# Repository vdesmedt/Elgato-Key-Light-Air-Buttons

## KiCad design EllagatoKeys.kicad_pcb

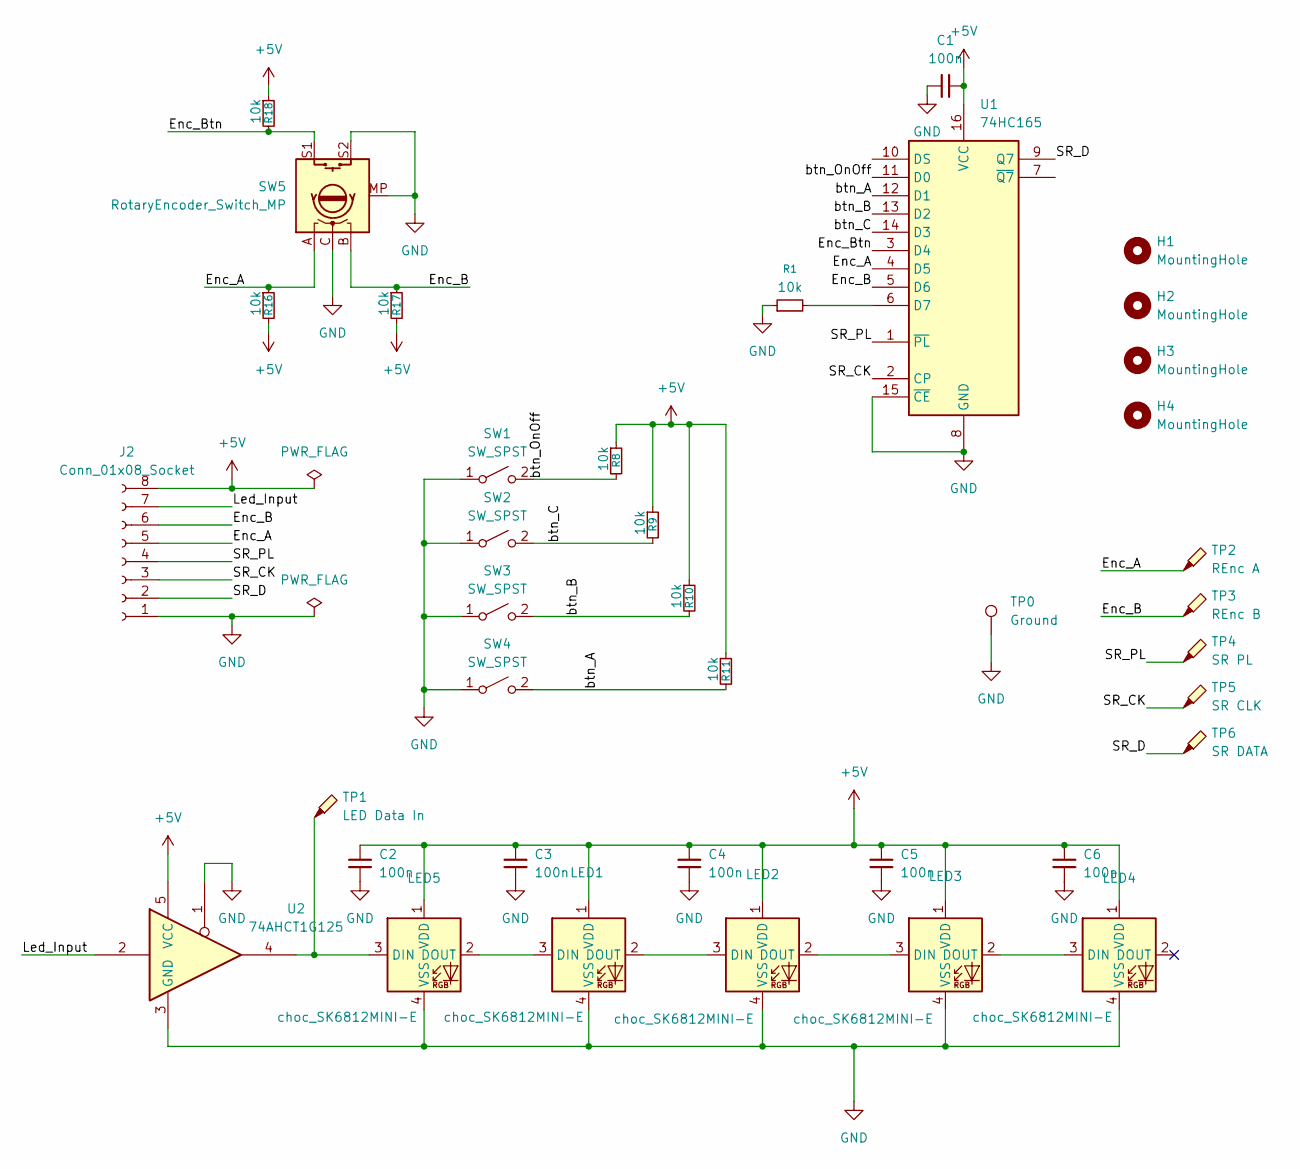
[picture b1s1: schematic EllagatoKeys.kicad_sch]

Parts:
C1, C2, C3, C4, C5, C6: 100n; C_0805_2012Metric_Pad1.18x1.45mm_HandSolder
H1, H2, H3, H4: MountingHole; MountingHole_2.7mm_M2.5
J2: Conn_01x08_Socket; PinHeader_1x08_P2.54mm_Horizontal
LED1, LED2, LED3, LED4, LED5: choc_SK6812MINI-E; LED_choc_6028R
R1, R8, R9, R10, R11, R16, R17, R18: 10k; R_0805_2012Metric_Pad1.20x1.40mm_HandSolder
SW1, SW2, SW3, SW4: SW_SPST; SW_Cherry_MX_1.00u_Plate
SW5: RotaryEncoder_Switch_MP; RotaryEncoder_Alps_EC11E-Switch_Vertical_H20mm
TP0: Ground; TestPoint_Keystone_5010-5014_Multipurpose
TP1: LED Data In; TestPoint_Keystone_5010-5014_Multipurpose
TP2: REnc A; TestPoint_Keystone_5010-5014_Multipurpose
TP3: REnc B; TestPoint_Keystone_5010-5014_Multipurpose
TP4: SR PL; TestPoint_Keystone_5010-5014_Multipurpose
TP5: SR CLK; TestPoint_Keystone_5010-5014_Multipurpose
TP6: SR DATA; TestPoint_Keystone_5010-5014_Multipurpose
U1: 74HC165; SOIC-16_3.9x9.9mm_P1.27mm
U2: 74AHCT1G125; SOT-23-5

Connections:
+5V: C1.2, C2.1, C3.1, C4.1, C5.1, C6.1, J2.8, LED1.1 (VDD), LED2.1 (VDD), LED3.1 (VDD), LED4.1 (VDD), LED5.1 (VDD), R8.1, R9.1, R10.1, R11.1, R16.2, R17.2, R18.1, U1.16 (VCC), U2.5 (VCC)
/Enc_A: J2.5, R16.1, SW5.A, TP2.1 (1_1), U1.4 (D5)
/Enc_B: J2.6, R17.1, SW5.B, TP3.1 (1_1), U1.5 (D6)
/Enc_Btn: R18.2, SW5.S1, U1.3 (D4)
/Led_Input: J2.7, U2.2
/SR_CK: J2.3, TP5.1 (1_1), U1.2 (CP)
/SR_D: J2.2, TP6.1 (1_1), U1.9 (Q7)
/SR_PL: J2.4, TP4.1 (1_1), U1.1 (~PL)
/btn_A: R11.2, SW4.2 (B), U1.12 (D1)
/btn_B: R10.2, SW3.2 (B), U1.13 (D2)
/btn_C: R9.2, SW2.2 (B), U1.14 (D3)
/btn_OnOff: R8.2, SW1.2 (B), U1.11 (D0)
GND: C1.1, C2.2, C3.2, C4.2, C5.2, C6.2, J2.1, LED1.4 (VSS), LED2.4 (VSS), LED3.4 (VSS), LED4.4 (VSS), LED5.4 (VSS), R1.1, SW1.1 (A), SW2.1 (A), SW3.1 (A), SW4.1 (A), SW5.C, SW5.MP, SW5.S2, TP0.1 (1_1), U1.8 (GND), U1.15 (~CE), U2.1, U2.3 (GND)
unnamed: LED1.3 (DIN), LED5.2 (DOUT)
unnamed: LED1.2 (DOUT), LED2.3 (DIN)
unnamed: LED2.2 (DOUT), LED3.3 (DIN)
unnamed: LED3.2 (DOUT), LED4.3 (DIN)
unnamed: LED5.3 (DIN), TP1.1 (1_1), U2.4
unnamed: R1.2, U1.6 (D7)

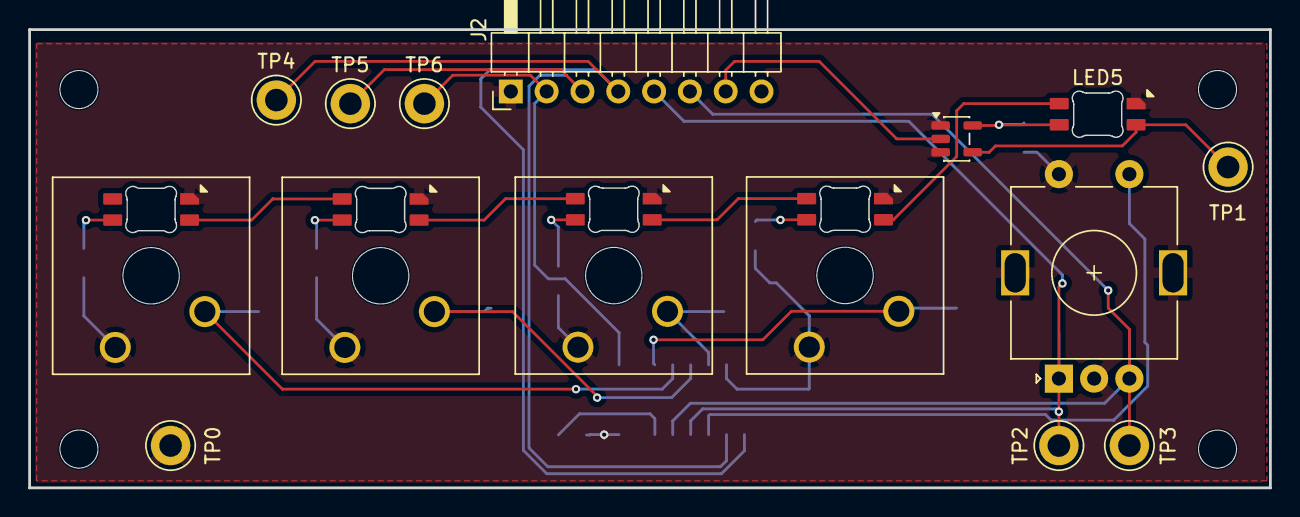
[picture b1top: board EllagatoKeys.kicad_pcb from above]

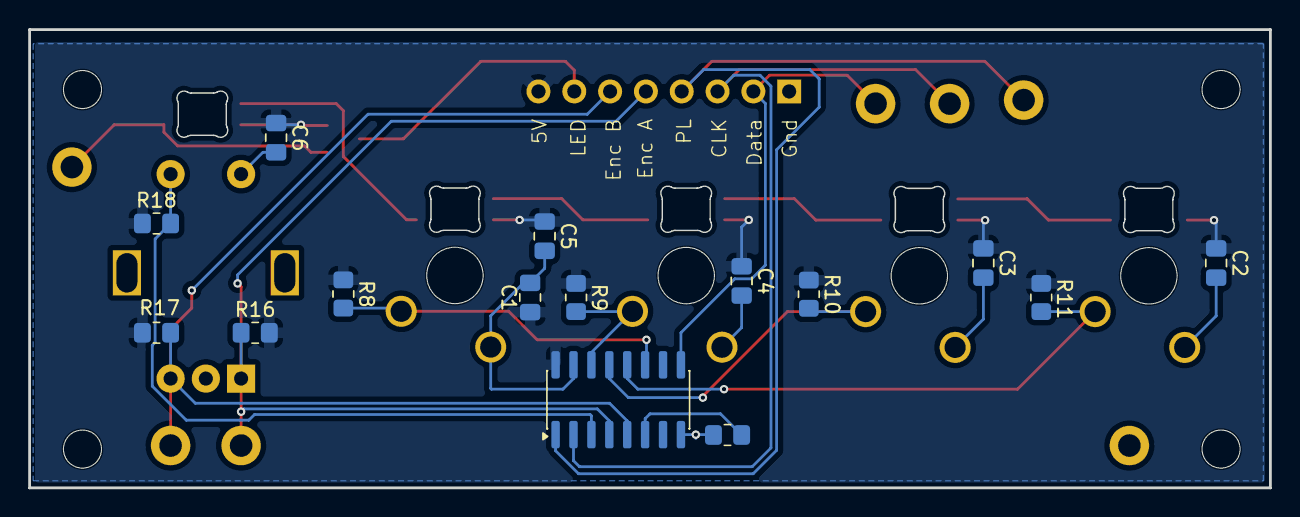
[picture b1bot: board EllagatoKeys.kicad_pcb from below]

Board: 2 copper layers, 88.0 x 32.5 mm, 38 parts (15 on the bottom side), 19 nets.
